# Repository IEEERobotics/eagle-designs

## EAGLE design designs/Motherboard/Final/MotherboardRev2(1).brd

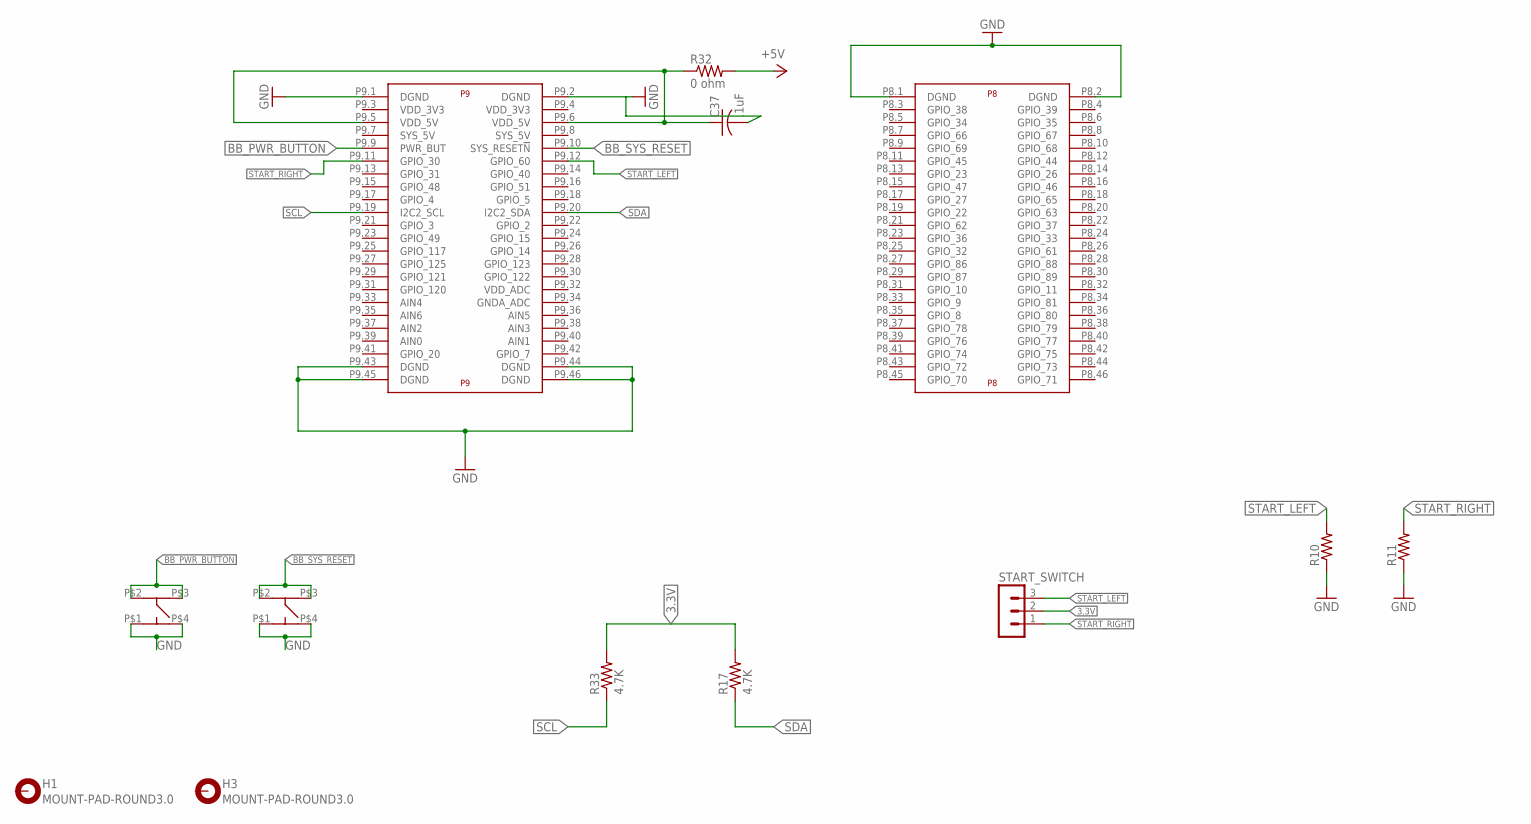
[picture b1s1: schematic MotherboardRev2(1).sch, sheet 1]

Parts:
C37: .1uF; C0402
H1, H3: MOUNT-PAD-ROUND3.0; 3,0-PAD
R10, R11: R-US_R0402; R0402
R17, R33: 4.7K; R0402
R32: 0 ohm; R0402
START_SWITCH: MA03-1
U$1: BEAGLE_BONE_BLACK_CAPE
U$13, U$14: Switch1; MC32882_FINAL

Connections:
3.3V: R17.2, R33.2, START_SWITCH.2; also elsewhere on the board
BB_PWR_BUTTON: U$1.P9.9 (PWR_BUT), U$13.P$2 (P2), U$13.P$3 (P3)
BB_SYS_RESET: U$1.P9.10 (SYS_RESET!N), U$14.P$2 (P2), U$14.P$3 (P3)
GND: C37.2, R10.1, R11.1, U$1.P8.1 (DGND), U$1.P8.2 (DGND), U$1.P9.1 (DGND), U$1.P9.2 (DGND), U$1.P9.43 (DGND), U$1.P9.44 (DGND), U$1.P9.45 (DGND), U$1.P9.46 (DGND), U$13.P$1 (P1), U$13.P$4 (P4), U$14.P$1 (P1), U$14.P$4 (P4); also elsewhere on the board
unnamed: C37.1, R32.1, U$1.P9.5 (VDD_5V), U$1.P9.6 (VDD_5V)
SCL: R33.1, U$1.P9.19 (I2C2_SCL); also elsewhere on the board
SDA: R17.1, U$1.P9.20 (I2C2_SDA); also elsewhere on the board
START_LEFT: R10.2, START_SWITCH.3, U$1.P9.12 (GPIO_60)
START_RIGHT: R11.2, START_SWITCH.1, U$1.P9.11 (GPIO_30)
VOUT1: R32.2; also elsewhere on the board

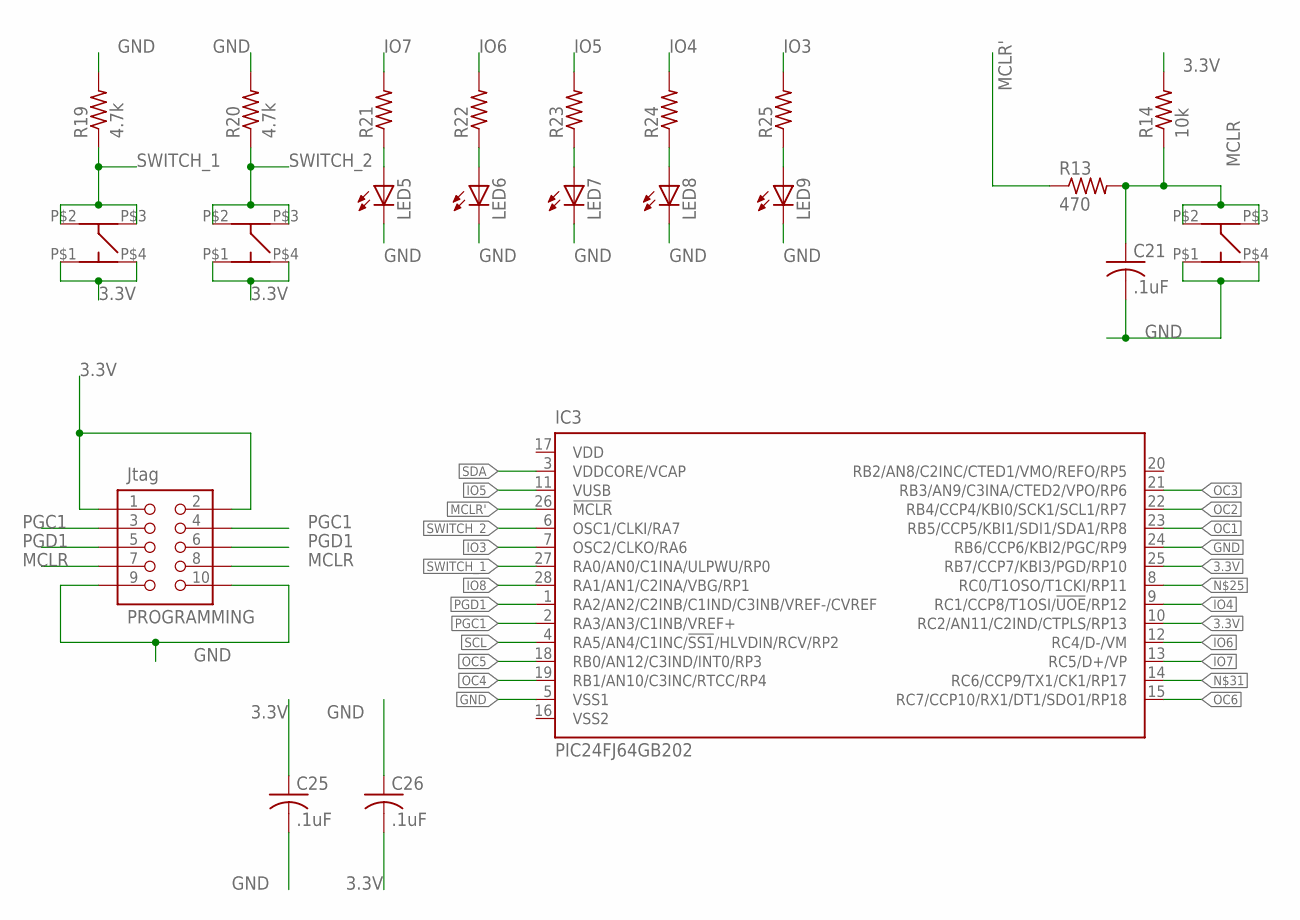
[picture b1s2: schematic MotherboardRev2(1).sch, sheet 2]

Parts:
C21, C25, C26: .1uF; C0402
IC3: PIC24FJ64GB202; QFN28-ML_6X6MM
LED5, LED6, LED7, LED8, LED9: LEDCHIPLED-0603-TTW; CHIPLED-0603-TTW
PROGRAMMING: Jtag; MOTHER-BOARD-REV5_10-PIN-SMD
R13: 470; R0402
R14: 10k; R0402
R19, R20: 4.7k; R0402
R21, R22, R23, R24, R25: R-US_R0402; R0402
U$5: Switch3; MC32882_FINAL
U$6: Switch1; MC32882_FINAL
U$7: Switch2; MC32882_FINAL

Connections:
3.3V: C25.1, C26.1, IC3.10 (RC2/AN11/C2IND/CTPLS/RP13), IC3.25 (RB7/CCP7/KBI3/PGD/RP10), PROGRAMMING.1, PROGRAMMING.2, R14.2, U$6.P$1 (P1), U$6.P$4 (P4), U$7.P$1 (P1), U$7.P$4 (P4); also elsewhere on the board
GND: C21.2, C25.2, C26.2, IC3.5 (VSS1), IC3.24 (RB6/CCP6/KBI2/PGC/RP9), LED5.C@1 (C), LED6.C@1 (C), LED7.C@1 (C), LED8.C@1 (C), LED9.C@1 (C), PROGRAMMING.9, PROGRAMMING.10, R19.2, R20.2, U$5.P$1 (P1), U$5.P$4 (P4); also elsewhere on the board
IO3: IC3.7 (OSC2/CLKO/RA6), R25.2
IO4: IC3.9 (RC1/CCP8/T1OSI/!UOE!/RP12), R24.2
IO5: IC3.11 (VUSB), R23.2
IO6: IC3.12 (RC4/D-/VM), R22.2
IO7: IC3.13 (RC5/D+/VP), R21.2
IO8: IC3.28 (RA1/AN1/C2INA/VBG/RP1)
MCLR: C21.1, PROGRAMMING.7, PROGRAMMING.8, R13.2, R14.1, U$5.P$2 (P2), U$5.P$3 (P3)
MCLR': IC3.26 (!MCLR), R13.1
unnamed: LED5.A@1 (A), R21.1
unnamed: LED6.A@1 (A), R22.1
unnamed: LED7.A@1 (A), R23.1
unnamed: LED8.A@1 (A), R24.1
unnamed: LED9.A@1 (A), R25.1
OC1: IC3.23 (RB5/CCP5/KBI1/SDI1/SDA1/RP8); also elsewhere on the board
OC2: IC3.22 (RB4/CCP4/KBI0/SCK1/SCL1/RP7); also elsewhere on the board
OC3: IC3.21 (RB3/AN9/C3INA/CTED2/VPO/RP6); also elsewhere on the board
OC4: IC3.19 (RB1/AN10/C3INC/RTCC/RP4); also elsewhere on the board
OC5: IC3.18 (RB0/AN12/C3IND/INT0/RP3); also elsewhere on the board
OC6: IC3.15 (RC7/CCP10/RX1/DT1/SDO1/RP18); also elsewhere on the board
PGC1: IC3.2 (RA3/AN3/C1INB/VREF+), PROGRAMMING.3, PROGRAMMING.4
PGD1: IC3.1 (RA2/AN2/C2INB/C1IND/C3INB/VREF-/CVREF), PROGRAMMING.5, PROGRAMMING.6
SCL: IC3.4 (RA5/AN4/C1INC/!SS1!/HLVDIN/RCV/RP2); also elsewhere on the board
SDA: IC3.3 (VDDCORE/VCAP); also elsewhere on the board
SWITCH_1: IC3.27 (RA0/AN0/C1INA/ULPWU/RP0), R19.1, U$6.P$2 (P2), U$6.P$3 (P3)
SWITCH_2: IC3.6 (OSC1/CLKI/RA7), R20.1, U$7.P$2 (P2), U$7.P$3 (P3)

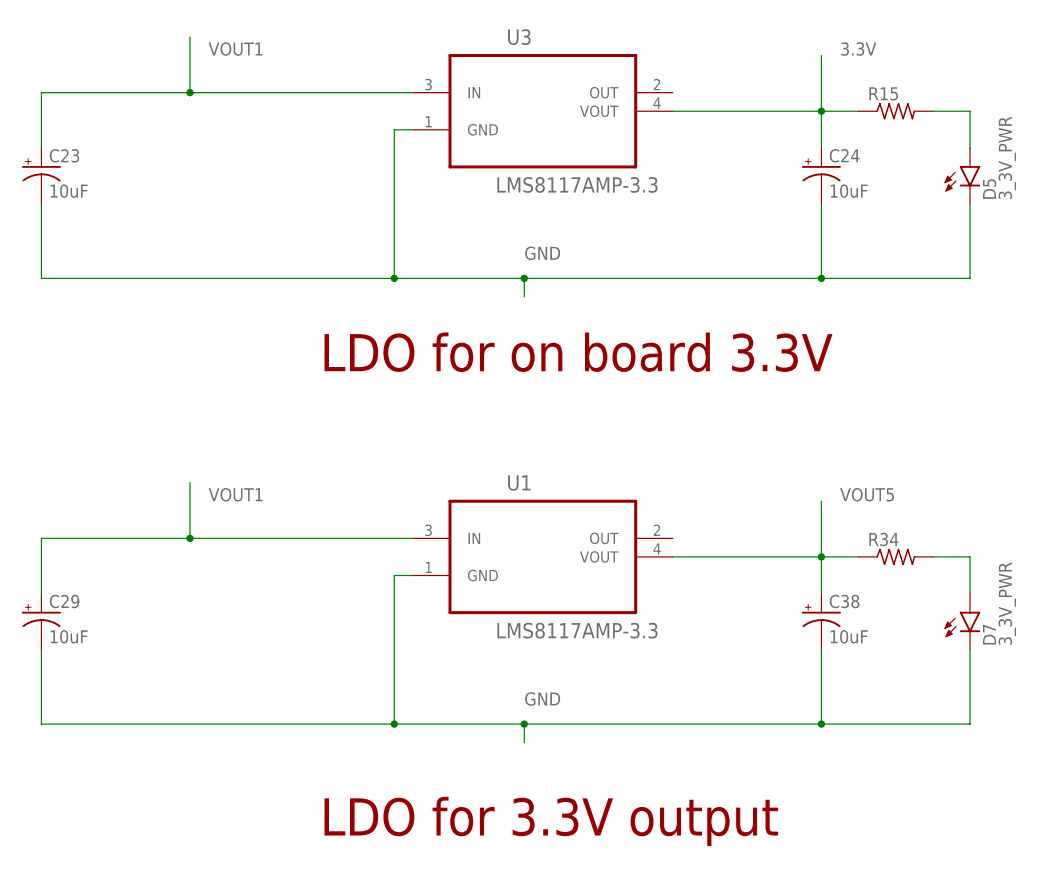
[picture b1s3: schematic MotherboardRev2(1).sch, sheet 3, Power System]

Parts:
C23, C24, C29, C38: 10uF; EIA3216
D5, D7: 3_3V_PWR; FKIT-LED-1206
R15, R34: R-US_R0805W; R0805W
U1, U3: LMS8117AMP-3.3; SOT230P696X180-4N

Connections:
3.3V: C24.A (+), R15.1, U3.4 (VOUT); also elsewhere on the board
GND: C23.C (-), C24.C (-), C29.C (-), C38.C (-), D5.C, D7.C, U1.1 (GND), U3.1 (GND); also elsewhere on the board
unnamed: D5.A, R15.2
unnamed: D7.A, R34.2
VOUT1: C23.A (+), C29.A (+), U1.3 (IN), U3.3 (IN); also elsewhere on the board
VOUT5: C38.A (+), R34.1, U1.4 (VOUT); also elsewhere on the board

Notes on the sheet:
LDO for on board 3.3V
LDO for 3.3V output

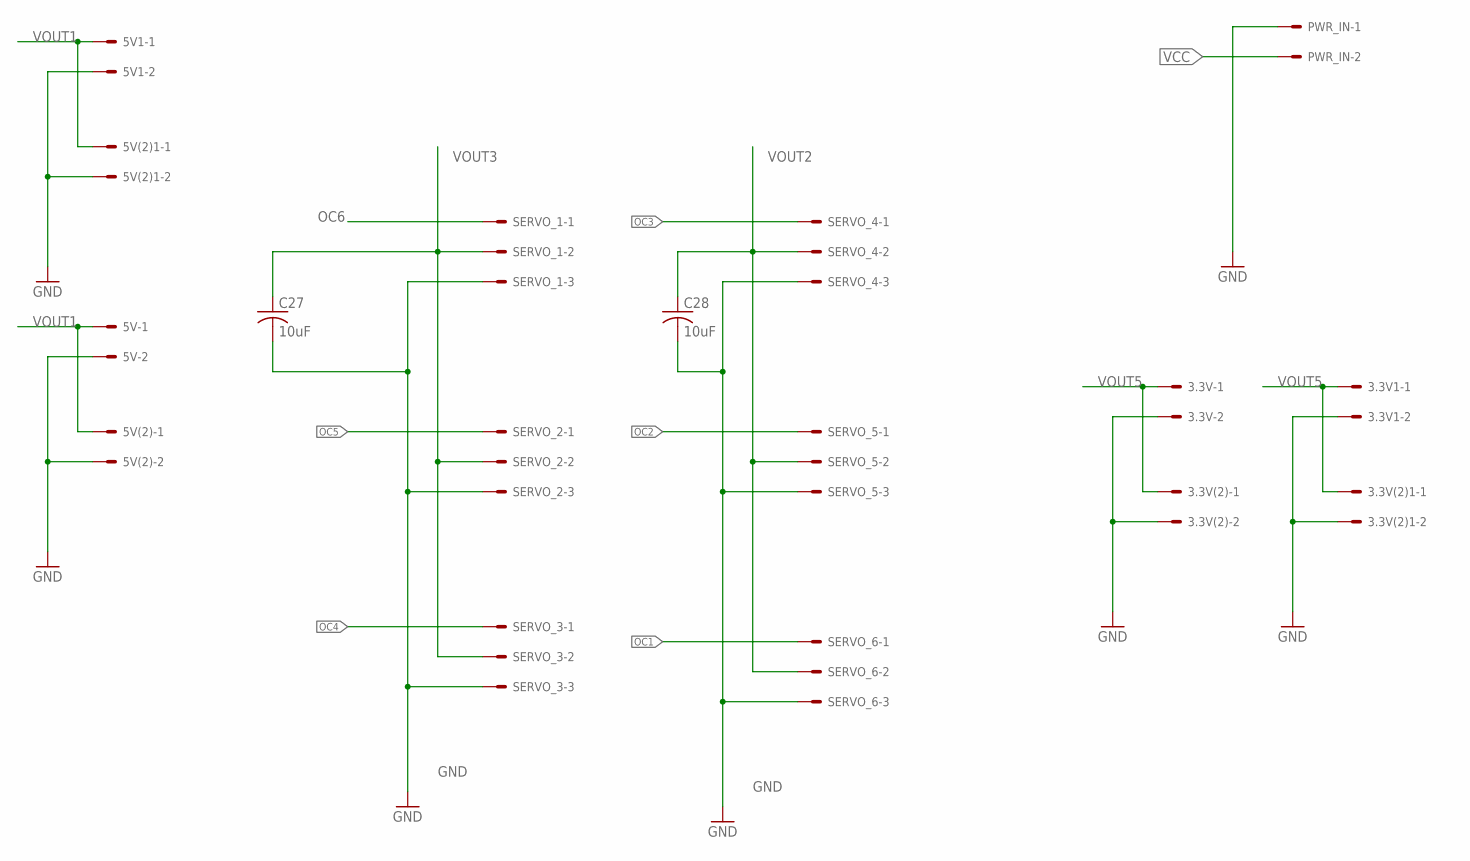
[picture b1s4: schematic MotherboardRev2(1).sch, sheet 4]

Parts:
3.3V, 3.3V1, 3.3V(2), 3.3V(2)1, 5V, 5V1, 5V(2), 5V(2)1: 22-05-7028-02; 7395-02
C27, C28: 10uF; C0805
PWR_IN: 555X-2H; 5569-2
SERVO_1, SERVO_2, SERVO_3, SERVO_4, SERVO_5, SERVO_6: 22-05-7038-03; 7395-03

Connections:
GND: 3.3V.2, 3.3V1.2, 3.3V(2).2, 3.3V(2)1.2, 5V.2, 5V1.2, 5V(2).2, 5V(2)1.2, C27.2, C28.2, PWR_IN.1, SERVO_1.3, SERVO_2.3, SERVO_3.3, SERVO_4.3, SERVO_5.3, SERVO_6.3; also elsewhere on the board
OC1: SERVO_6.1; also elsewhere on the board
OC2: SERVO_5.1; also elsewhere on the board
OC3: SERVO_4.1; also elsewhere on the board
OC4: SERVO_3.1; also elsewhere on the board
OC5: SERVO_2.1; also elsewhere on the board
OC6: SERVO_1.1; also elsewhere on the board
VCC: PWR_IN.2; also elsewhere on the board
VOUT1: 5V.1, 5V1.1, 5V(2).1, 5V(2)1.1; also elsewhere on the board
VOUT2: C28.1, SERVO_4.2, SERVO_5.2, SERVO_6.2; also elsewhere on the board
VOUT3: C27.1, SERVO_1.2, SERVO_2.2, SERVO_3.2; also elsewhere on the board
VOUT5: 3.3V.1, 3.3V1.1, 3.3V(2).1, 3.3V(2)1.1; also elsewhere on the board

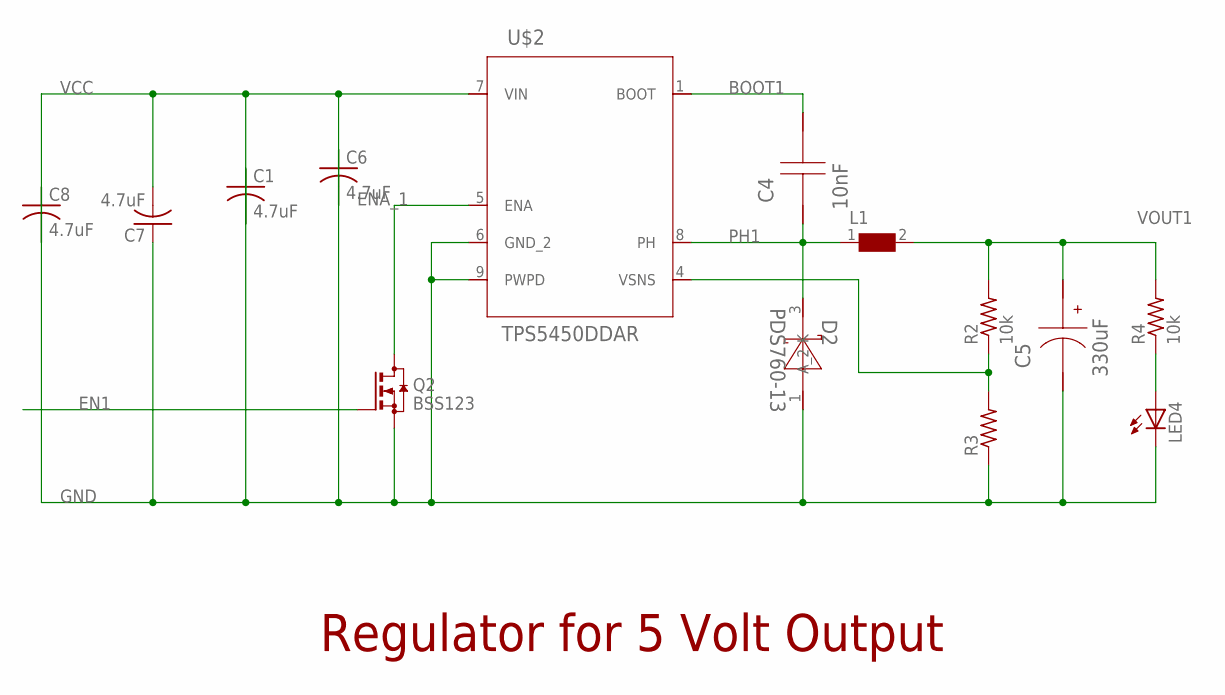
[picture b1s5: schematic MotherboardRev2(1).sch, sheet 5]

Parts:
C1, C6, C7, C8: 4.7uF; C0805
C4: 10nF; 0805
C5: 330uF; SM_RADIAL_10AMM
D2: PDS760-13; POWERDI5
L1: WE-HCC-7443331000_1090; WE-HCC_1090
LED4: LEDSML1206; SML1206
Q2: BSS123; SOT23
R2, R4: 10k; R1206
R3: R-US_R1206; R1206
U$2: TPS5450DDAR; R-PDSO-G8

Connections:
BOOT1: C4.1, U$2.1 (BOOT)
EN1: Q2.1 (G)
ENA_1: Q2.3 (D), U$2.5 (ENA)
GND: C1.1, C5.2 (-), C6.1, C7.1, C8.1, D2.1 (A_2), LED4.C, Q2.2 (S), R3.1, U$2.6 (GND_2), U$2.9 (PWPD); also elsewhere on the board
unnamed: LED4.A, R4.1
PH1: C4.2, D2.3 (K), L1.1, U$2.8 (PH)
VCC: C1.2, C6.2, C7.2, C8.2, U$2.7 (VIN); also elsewhere on the board
VOUT1: C5.1 (+), L1.2, R2.2, R4.2; also elsewhere on the board
VSNS1: R2.1, R3.2, U$2.4 (VSNS)

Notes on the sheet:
Regulator for 5 Volt Output

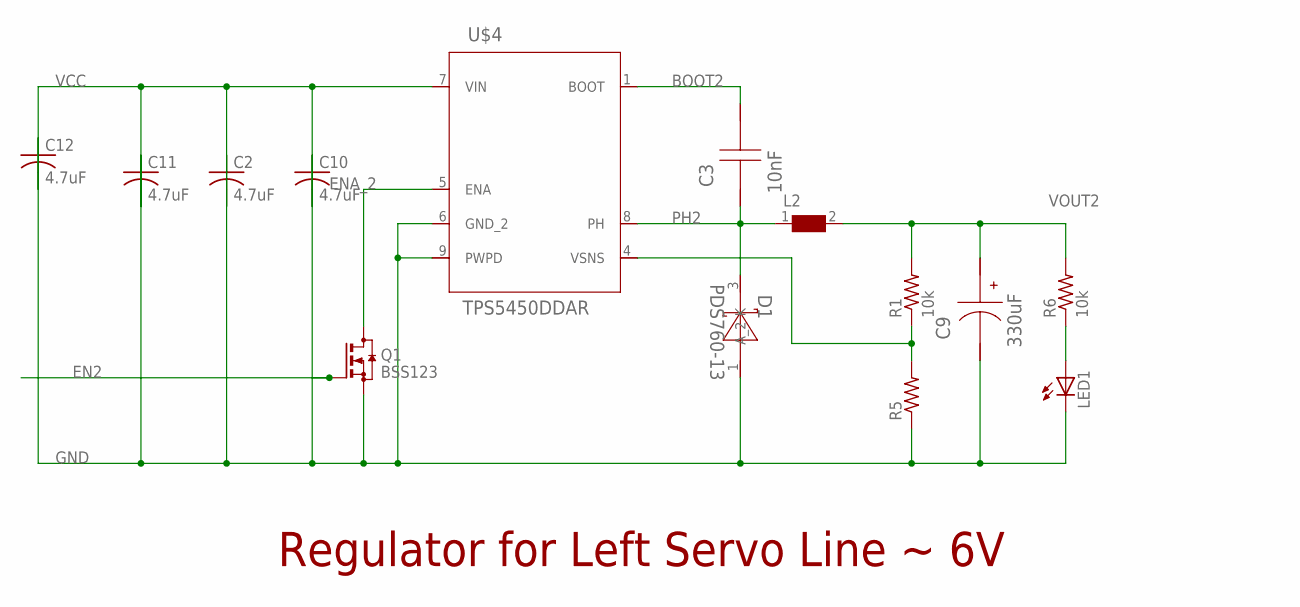
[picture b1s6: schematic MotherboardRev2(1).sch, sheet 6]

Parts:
C2, C10, C11, C12: 4.7uF; C0805
C3: 10nF; 0805
C9: 330uF; SM_RADIAL_10AMM
D1: PDS760-13; POWERDI5
L2: WE-HCC-7443331000_1090; WE-HCC_1090
LED1: LEDSML1206; SML1206
Q1: BSS123; SOT23
R1, R6: 10k; R1206
R5: R-US_R1206; R1206
U$4: TPS5450DDAR; R-PDSO-G8

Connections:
BOOT2: C3.1, U$4.1 (BOOT)
EN2: Q1.1 (G)
ENA_2: Q1.3 (D), U$4.5 (ENA)
GND: C2.1, C9.2 (-), C10.1, C11.1, C12.1, D1.1 (A_2), LED1.C, Q1.2 (S), R5.1, U$4.6 (GND_2), U$4.9 (PWPD); also elsewhere on the board
unnamed: LED1.A, R6.1
PH2: C3.2, D1.3 (K), L2.1, U$4.8 (PH)
VCC: C2.2, C10.2, C11.2, C12.2, U$4.7 (VIN); also elsewhere on the board
VOUT2: C9.1 (+), L2.2, R1.2, R6.2; also elsewhere on the board
VSNS2: R1.1, R5.2, U$4.4 (VSNS)

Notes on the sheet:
Regulator for Left Servo Line ~ 6V

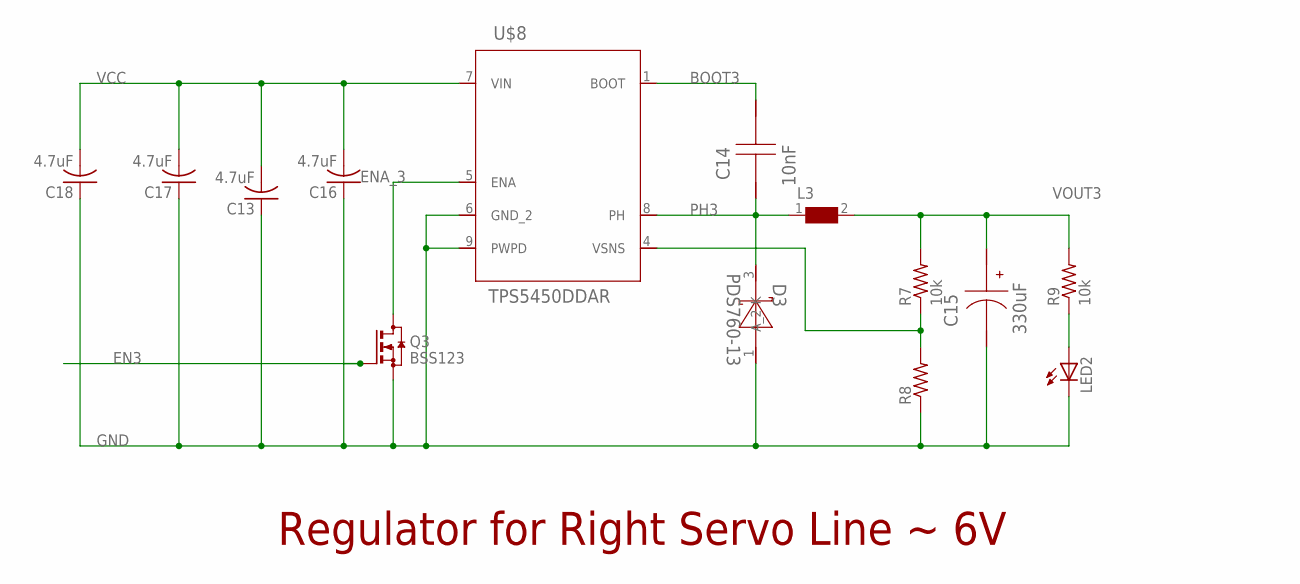
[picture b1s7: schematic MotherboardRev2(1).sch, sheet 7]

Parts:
C13, C16, C17, C18: 4.7uF; C0805
C14: 10nF; 0805
C15: 330uF; SM_RADIAL_10AMM
D3: PDS760-13; POWERDI5
L3: WE-HCC-7443331000_1090; WE-HCC_1090
LED2: LEDSML1206; SML1206
Q3: BSS123; SOT23
R7, R9: 10k; R1206
R8: R-US_R1206; R1206
U$8: TPS5450DDAR; R-PDSO-G8

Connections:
BOOT3: C14.1, U$8.1 (BOOT)
EN3: Q3.1 (G)
ENA_3: Q3.3 (D), U$8.5 (ENA)
GND: C13.1, C15.2 (-), C16.1, C17.1, C18.1, D3.1 (A_2), LED2.C, Q3.2 (S), R8.1, U$8.6 (GND_2), U$8.9 (PWPD); also elsewhere on the board
unnamed: LED2.A, R9.1
PH3: C14.2, D3.3 (K), L3.1, U$8.8 (PH)
VCC: C13.2, C16.2, C17.2, C18.2, U$8.7 (VIN); also elsewhere on the board
VOUT3: C15.1 (+), L3.2, R7.2, R9.2; also elsewhere on the board
VSNS3: R7.1, R8.2, U$8.4 (VSNS)

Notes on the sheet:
Regulator for Right Servo Line ~ 6V

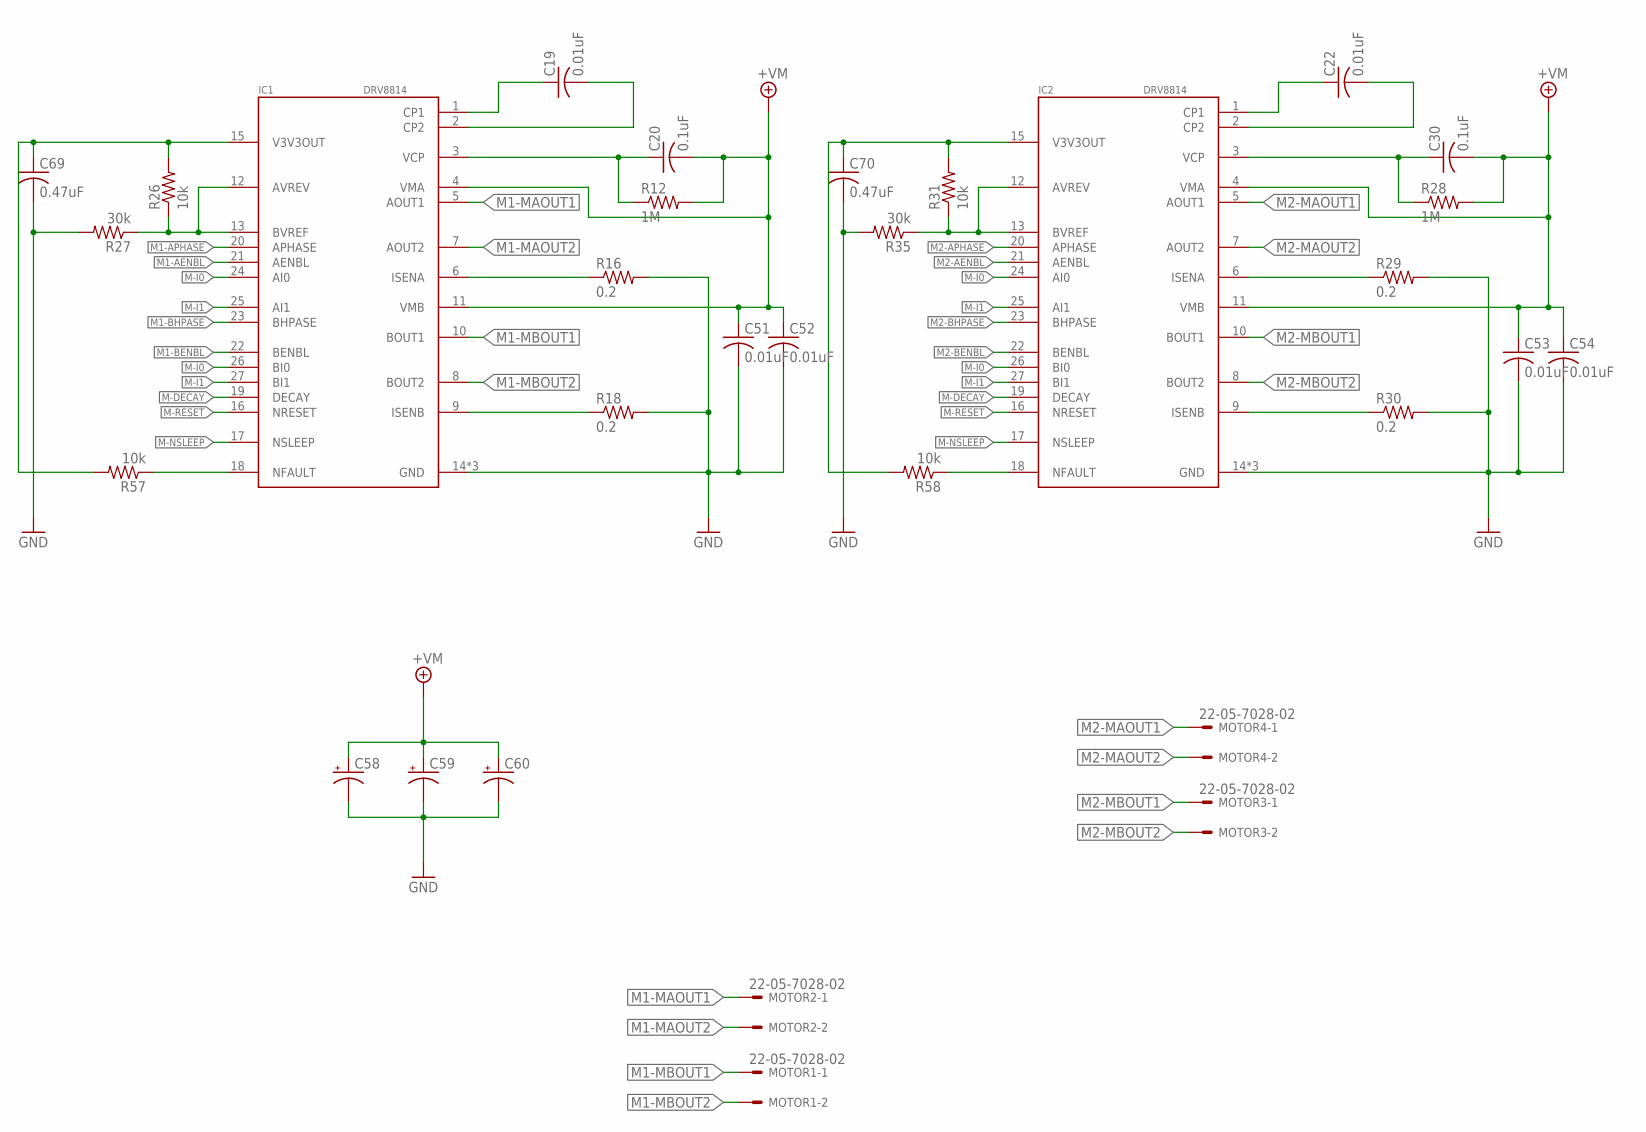
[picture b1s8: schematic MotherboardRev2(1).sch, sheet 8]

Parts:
C19, C22, C51, C52, C53, C54: 0.01uF; C0402
C20, C30: 0.1uF; C0402
C58, C59, C60: CPOL-US153CLV-0605; 153CLV-0605
C69, C70: 0.47uF; C0402
IC1, IC2: DRV8814; TSSOP-28
MOTOR1, MOTOR2, MOTOR3, MOTOR4: 22-05-7028-02; 7395-02
R12, R28: 1M; R0402
R16, R18, R29, R30: 0.2; R0402
R26, R31, R57, R58: 10k; R0402
R27, R35: 30k; R0402

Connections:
+7V: C20.2, C30.2, C51.1, C52.1, C53.1, C54.1, C58.+, C59.+, C60.+, IC1.4 (VMA), IC1.11 (VMB), IC2.4 (VMA), IC2.11 (VMB), R12.2, R28.2; also elsewhere on the board
GND: C51.2, C52.2, C53.2, C54.2, C58.-, C59.-, C60.-, C69.2, C70.2, IC1.14 (GND), IC1.28 (GND), IC1.EXP (GND), IC2.14 (GND), IC2.28 (GND), IC2.EXP (GND), R16.2, R18.2, R27.2, R29.2, R30.2, R35.2; also elsewhere on the board
M1-AENBL: IC1.21 (AENBL); also elsewhere on the board
M1-APHASE: IC1.20 (APHASE); also elsewhere on the board
M1-BENBL: IC1.22 (BENBL); also elsewhere on the board
M1-BHPASE: IC1.23 (BHPASE); also elsewhere on the board
M1-MAOUT1: IC1.5 (AOUT1), MOTOR2.1
M1-MAOUT2: IC1.7 (AOUT2), MOTOR2.2
M1-MBOUT1: IC1.10 (BOUT1), MOTOR1.1
M1-MBOUT2: IC1.8 (BOUT2), MOTOR1.2
M2-AENBL: IC2.21 (AENBL); also elsewhere on the board
M2-APHASE: IC2.20 (APHASE); also elsewhere on the board
M2-BENBL: IC2.22 (BENBL); also elsewhere on the board
M2-BHPASE: IC2.23 (BHPASE); also elsewhere on the board
M2-MAOUT1: IC2.5 (AOUT1), MOTOR4.1
M2-MAOUT2: IC2.7 (AOUT2), MOTOR4.2
M2-MBOUT1: IC2.10 (BOUT1), MOTOR3.1
M2-MBOUT2: IC2.8 (BOUT2), MOTOR3.2
M-DECAY: IC1.19 (DECAY), IC2.19 (DECAY); also elsewhere on the board
M-I0: IC1.24 (AI0), IC1.26 (BI0), IC2.24 (AI0), IC2.26 (BI0); also elsewhere on the board
M-I1: IC1.25 (AI1), IC1.27 (BI1), IC2.25 (AI1), IC2.27 (BI1); also elsewhere on the board
M-NSLEEP: IC1.17 (NSLEEP), IC2.17 (NSLEEP); also elsewhere on the board
M-RESET: IC1.16 (NRESET), IC2.16 (NRESET); also elsewhere on the board
unnamed: C19.2, IC1.2 (CP2)
unnamed: C19.1, IC1.1 (CP1)
unnamed: C20.1, IC1.3 (VCP), R12.1
unnamed: IC1.6 (ISENA), R16.1
unnamed: IC1.9 (ISENB), R18.1
unnamed: IC1.12 (AVREV), IC1.13 (BVREF), R26.1, R27.1
unnamed: C22.2, IC2.2 (CP2)
unnamed: C22.1, IC2.1 (CP1)
unnamed: C30.1, IC2.3 (VCP), R28.1
unnamed: IC2.6 (ISENA), R29.1
unnamed: IC2.9 (ISENB), R30.1
unnamed: IC2.12 (AVREV), IC2.13 (BVREF), R31.1, R35.1
unnamed: IC1.18 (NFAULT), R57.1
unnamed: C69.1, IC1.15 (V3V3OUT), R26.2, R57.2
unnamed: IC2.18 (NFAULT), R58.1
unnamed: C70.1, IC2.15 (V3V3OUT), R31.2, R58.2

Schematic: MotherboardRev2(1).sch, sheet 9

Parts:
C31, C32, C39, C40: 1nF; C0402
C33, C45, C46, C47, C48, C49, C50: 0.1uF; C0402
C34, C35, C36, C42, C43, C44: 0.22uF; C0402
C41: .1uF; C0402
R36, R37, R44, R45: 0.1; R0402
R38, R39, R46, R47: 47k; R0402
R40, R41, R42, R43, R48, R49, R50, R51: 10k; R0402
STEP1, STEP2: 22-05-7048-04; 7395-04
U2, U4: DRV8811PWP; SOP65P640X120-29N

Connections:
3.3V: C49.1, C50.1, R40.1, R43.1, R48.1, R51.1, U2.10 (VCC), U4.10 (VCC); also elsewhere on the board
+7V: C36.1, C44.1, C45.1, C46.1, C47.1, C48.1, U2.15 (VMB), U2.28 (VMA), U4.15 (VMB), U4.28 (VMA); also elsewhere on the board
GND: C31.2, C32.2, C33.2, C35.2, C39.2, C40.2, C41.2, C43.2, C45.2, C46.2, C47.2, C48.2, C49.2, C50.2, R36.2, R37.2, R38.2, R39.2, R41.2, R42.2, R44.2, R45.2, R46.2, R47.2, R49.2, R50.2, U2.7 (GND_2), U2.21 (GND), U2.29 (EP), U4.7 (GND_2), U4.21 (GND), U4.29 (EP); also elsewhere on the board
M-NSLEEP: U2.27 (SLEEPN), U4.27 (SLEEPN); also elsewhere on the board
M-RESET: U2.17 (RESETN), U4.17 (RESETN); also elsewhere on the board
unnamed: R37.1, U2.14 (ISENB)
unnamed: R36.1, U2.1 (ISENA)
unnamed: C31.1, R38.1, U2.6 (RCA)
unnamed: C32.1, R39.1, U2.9 (RCB)
unnamed: C33.1, R40.2, R41.1, U2.5 (DECAY)
unnamed: R42.1, R43.2, U2.8 (VREF)
unnamed: C34.1, U2.23 (CP1)
unnamed: C34.2, U2.24 (CP2)
unnamed: C35.1, U2.20 (VGD)
unnamed: C36.2, U2.22 (VCP)
unnamed: R45.1, U4.14 (ISENB)
unnamed: R44.1, U4.1 (ISENA)
unnamed: C39.1, R46.1, U4.6 (RCA)
unnamed: C40.1, R47.1, U4.9 (RCB)
unnamed: C41.1, R48.2, R49.1, U4.5 (DECAY)
unnamed: R50.1, R51.2, U4.8 (VREF)
unnamed: C42.1, U4.23 (CP1)
unnamed: C42.2, U4.24 (CP2)
unnamed: C43.1, U4.20 (VGD)
unnamed: C44.2, U4.22 (VCP)
S1-AOUT1: STEP1.4, U2.4 (AOUT1)
S1-AOUT2: STEP1.1, U2.25 (AOUT2)
S1-BOUT1: STEP1.3, U2.11 (BOUT1)
S1-BOUT2: STEP1.2, U2.18 (BOUT2)
S1-DIR: U2.3 (DIR); also elsewhere on the board
S1-ENABLEN: U2.26 (ENABLEN); also elsewhere on the board
S1-HOME: U2.2 (HOME); also elsewhere on the board
S1-STEP: U2.19 (STEP); also elsewhere on the board
S2-AOUT1: STEP2.4, U4.4 (AOUT1)
S2-AOUT2: STEP2.1, U4.25 (AOUT2)
S2-BOUT1: STEP2.3, U4.11 (BOUT1)
S2-BOUT2: STEP2.2, U4.18 (BOUT2)
S2-DIR: U4.3 (DIR); also elsewhere on the board
S2-ENABLEN: U4.26 (ENABLEN); also elsewhere on the board
S2-HOME: U4.2 (HOME); also elsewhere on the board
S2-STEP: U4.19 (STEP); also elsewhere on the board
S-SRN: U2.16 (SRN), U4.16 (SRN); also elsewhere on the board
USM0: U2.13 (USM0), U4.13 (USM0); also elsewhere on the board
USM1: U2.12 (USM1), U4.12 (USM1); also elsewhere on the board

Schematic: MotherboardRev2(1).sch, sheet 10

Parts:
C55: 1uF; C0402
C56, C57: 0.1uF; C0402
C61: 10uF; C0805
C68: .1uF; C0402
H2, H4: MOUNT-PAD-ROUND3.0; 3,0-PAD
IC4: PIC24FJ256GB106; TQFP64-10X10
MOTIN1, MOTIN2, MOTIN3, MOTIN4: 22-05-7048-04; 7395-04
PROGRAMMING1: Jtag; MOTHER-BOARD-REV5_10-PIN-SMD
PWR_IN(2): 555X-2H; 5569-2
R55: 100; R0402
R56: 10k; R0402
SERVO_7, SERVO_8, SERVO_9: 22-05-7038-03; 7395-03
TP1, TP2: PTR1B1,27; B1,27
U$9: Switch3; MC32882_FINAL

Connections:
3.3V: C55.1, C56.1, C57.1, IC4.10 (VDD), IC4.26 (VDD), IC4.38 (VDD), PROGRAMMING1.1, PROGRAMMING1.2, R56.2; also elsewhere on the board
+7V: C61.1, H4.B3,0, MOTIN1.2, MOTIN2.2, MOTIN3.2, MOTIN4.2, SERVO_7.2, SERVO_8.2, SERVO_9.2; also elsewhere on the board
AVDD: IC4.19 (AVDD)
AVSS: IC4.20 (AVSS)
CHANNEL_A_1: IC4.4 (RG6), MOTIN1.4
CHANNEL_A_2: IC4.22 (RB9), MOTIN2.3
CHANNEL_A_3: IC4.18 (RB7), MOTIN3.3
CHANNEL_A_4: IC4.8 (RG9), MOTIN4.3
CHANNEL_B_1: IC4.5 (RG7), MOTIN1.3
CHANNEL_B_2: IC4.21 (RB8), MOTIN2.4
CHANNEL_B_3: IC4.17 (RB6), MOTIN3.4
CHANNEL_B_4: IC4.6 (RG8), MOTIN4.4
GND: C55.2, C56.2, C57.2, C61.2, C68.2, IC4.9 (VSS), IC4.25 (VSS), IC4.41 (VSS), MOTIN1.1, MOTIN2.1, MOTIN3.1, MOTIN4.1, PROGRAMMING1.9, PROGRAMMING1.10, PWR_IN(2).1, SERVO_7.3, SERVO_8.3, SERVO_9.3, U$9.P$1 (P1), U$9.P$4 (P4); also elsewhere on the board
M1-AENBL: IC4.47 (RC13); also elsewhere on the board
M1-APHASE: IC4.48 (RC14); also elsewhere on the board
M1-BENBL: IC4.46 (RD0); also elsewhere on the board
M1-BHPASE: IC4.45 (RD11); also elsewhere on the board
M2-AENBL: IC4.39 (RC12); also elsewhere on the board
M2-APHASE: IC4.43 (RD9); also elsewhere on the board
M2-BENBL: IC4.37 (RG2); also elsewhere on the board
M2-BHPASE: IC4.42 (RD8); also elsewhere on the board
M-DECAY: IC4.49 (RD1); also elsewhere on the board
M-I0: IC4.44 (RD10); also elsewhere on the board
M-I1: IC4.40 (RC15); also elsewhere on the board
M-NSLEEP: IC4.58 (RF0); also elsewhere on the board
M-RESET: IC4.60 (RE0); also elsewhere on the board
M_MCLR: C68.1, PROGRAMMING1.7, PROGRAMMING1.8, R55.2, R56.1, U$9.P$2 (P2), U$9.P$3 (P3)
M_MCLR': IC4.7 (!MCLR), R55.1
M_PGC1: IC4.15 (RB1), PROGRAMMING1.3, PROGRAMMING1.4
M_PGD1: IC4.16 (RB0), PROGRAMMING1.5, PROGRAMMING1.6
OC1': IC4.33 (RF3), SERVO_7.1
OC2': IC4.32 (RF5), SERVO_8.1
OC3': IC4.31 (RF4), SERVO_9.1
S1-DIR: IC4.64 (RE4); also elsewhere on the board
S1-ENABLEN: IC4.55 (RD7); also elsewhere on the board
S1-HOME: IC4.63 (RE3); also elsewhere on the board
S1-STEP: IC4.53 (RD5); also elsewhere on the board
S2-DIR: IC4.54 (RD6); also elsewhere on the board
S2-ENABLEN: IC4.51 (RD3); also elsewhere on the board
S2-HOME: IC4.52 (RD4); also elsewhere on the board
S2-STEP: IC4.50 (RD2); also elsewhere on the board
S-SRN: IC4.59 (RF1); also elsewhere on the board
SCL: IC4.2 (RE6), TP1.TP; also elsewhere on the board
SDA: IC4.3 (RE7), TP2.TP; also elsewhere on the board
USM0: IC4.62 (RE2); also elsewhere on the board
USM1: IC4.61 (RE1); also elsewhere on the board
VCC: PWR_IN(2).2; also elsewhere on the board
VDDCORE: IC4.56 (VDDCORE)

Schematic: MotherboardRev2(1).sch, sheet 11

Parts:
C62, C65, C66, C67: 4.7uF; 1206
C63: 10nF; 0805
C64: 330uF; SM_RADIAL_10AMM
D4: PDS760-13; POWERDI5
L4: WE-HCC-7443331000_1090; WE-HCC_1090
LED3: LEDCHIP-LED0603; CHIP-LED0603
POWER_ON: LEDCHIP-LED0603; CHIP-LED0603
R52, R54, R59: 10k; R0402
R53: R-US_R0402; R0402
U$3: TPS5450DDAR; R-PDSO-G8
U$10: LOGO

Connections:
+7V: C64.1 (+), L4.2, R52.2, R54.2; also elsewhere on the board
BOOT_VM: C63.1, U$3.1 (BOOT)
GND: C62.1, C64.2 (-), C65.1, C66.1, C67.1, D4.1 (A_2), LED3.C, POWER_ON.C, R53.1, U$3.6 (GND_2), U$3.9 (PWPD); also elsewhere on the board
unnamed: LED3.A, R54.1
unnamed: POWER_ON.A, R59.1
PH_VM: C63.2, D4.3 (K), L4.1, U$3.8 (PH)
VCC: C62.2, C65.2, C66.2, C67.2, R59.2, U$3.7 (VIN); also elsewhere on the board
VSNS_VM: R52.1, R53.2, U$3.4 (VSNS)

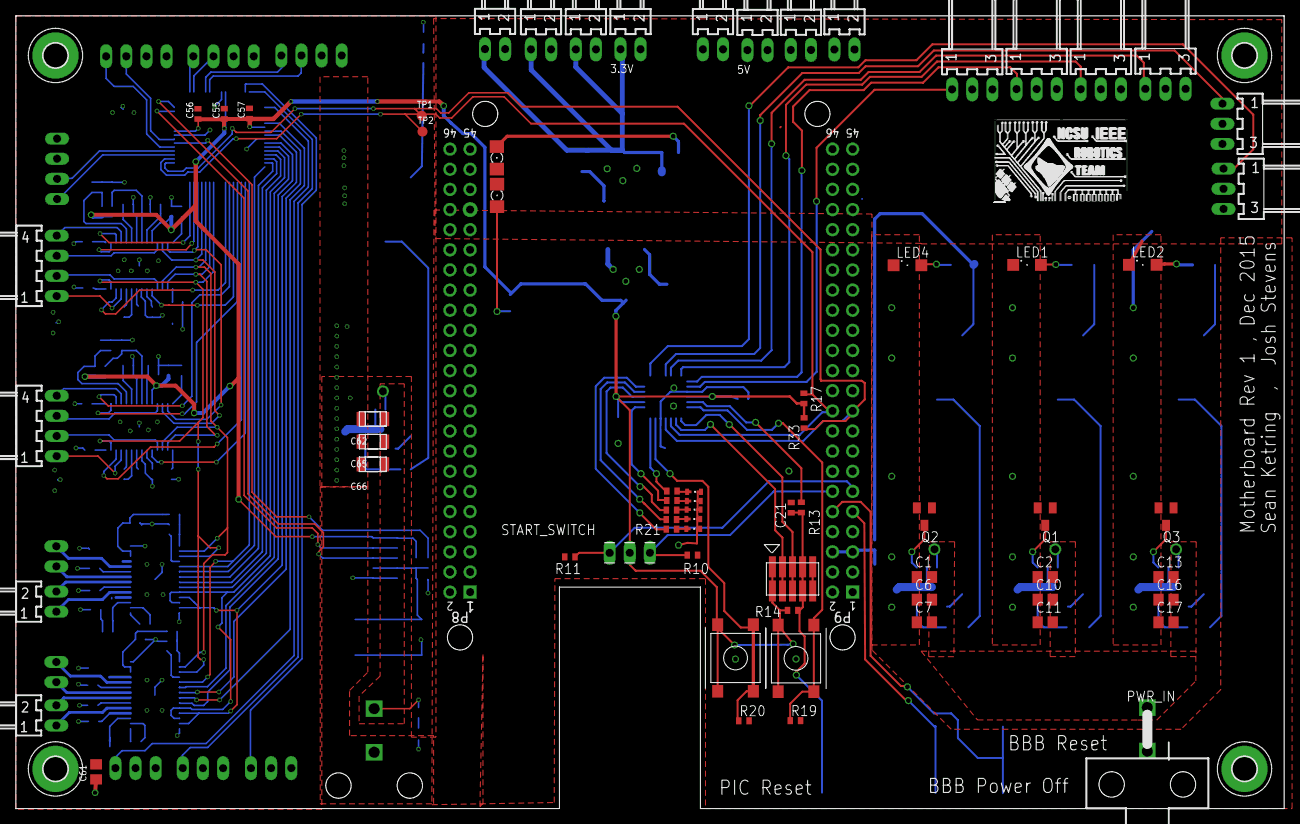
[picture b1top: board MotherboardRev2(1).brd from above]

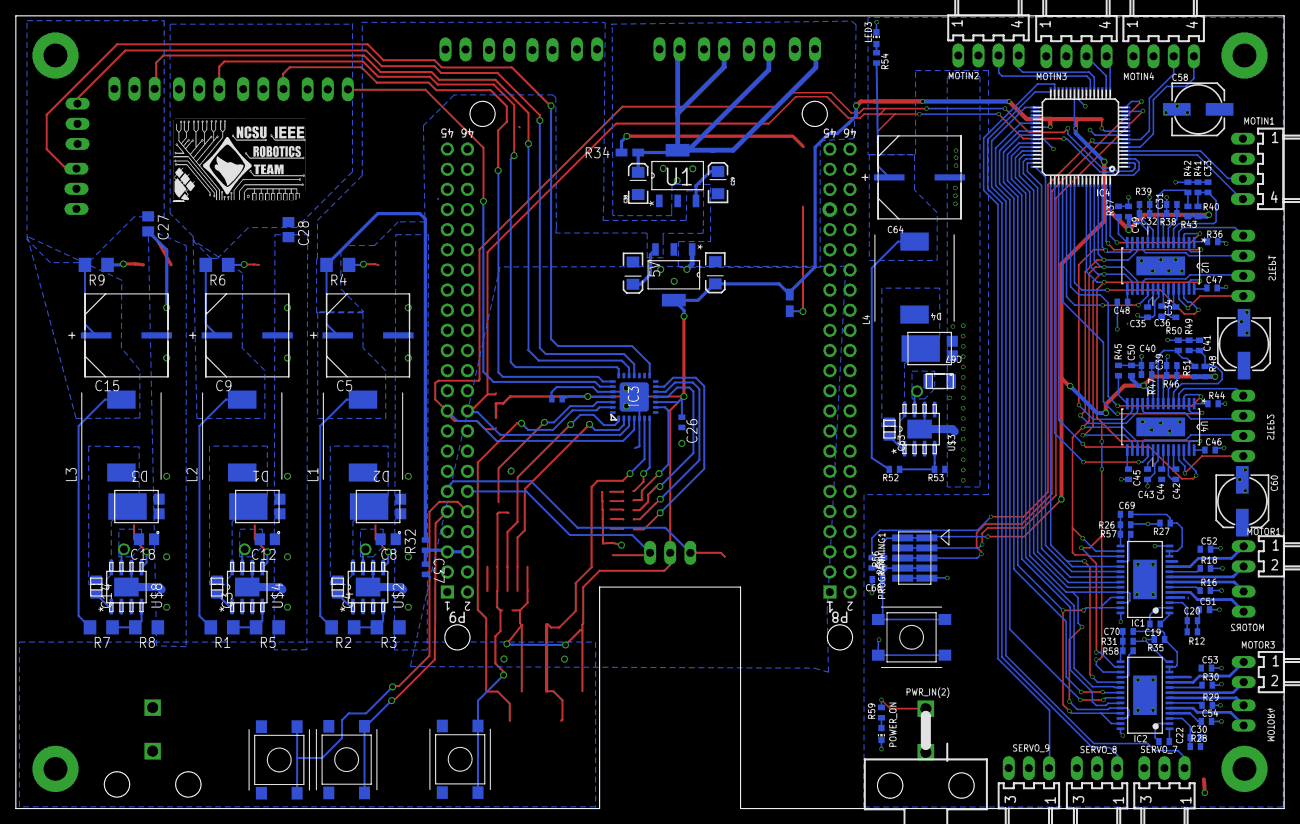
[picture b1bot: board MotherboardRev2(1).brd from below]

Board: 2 copper layers, 160.0 x 100.0 mm, 212 parts (137 on the bottom side), 150 nets.

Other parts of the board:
U$11, U$12: LOGO

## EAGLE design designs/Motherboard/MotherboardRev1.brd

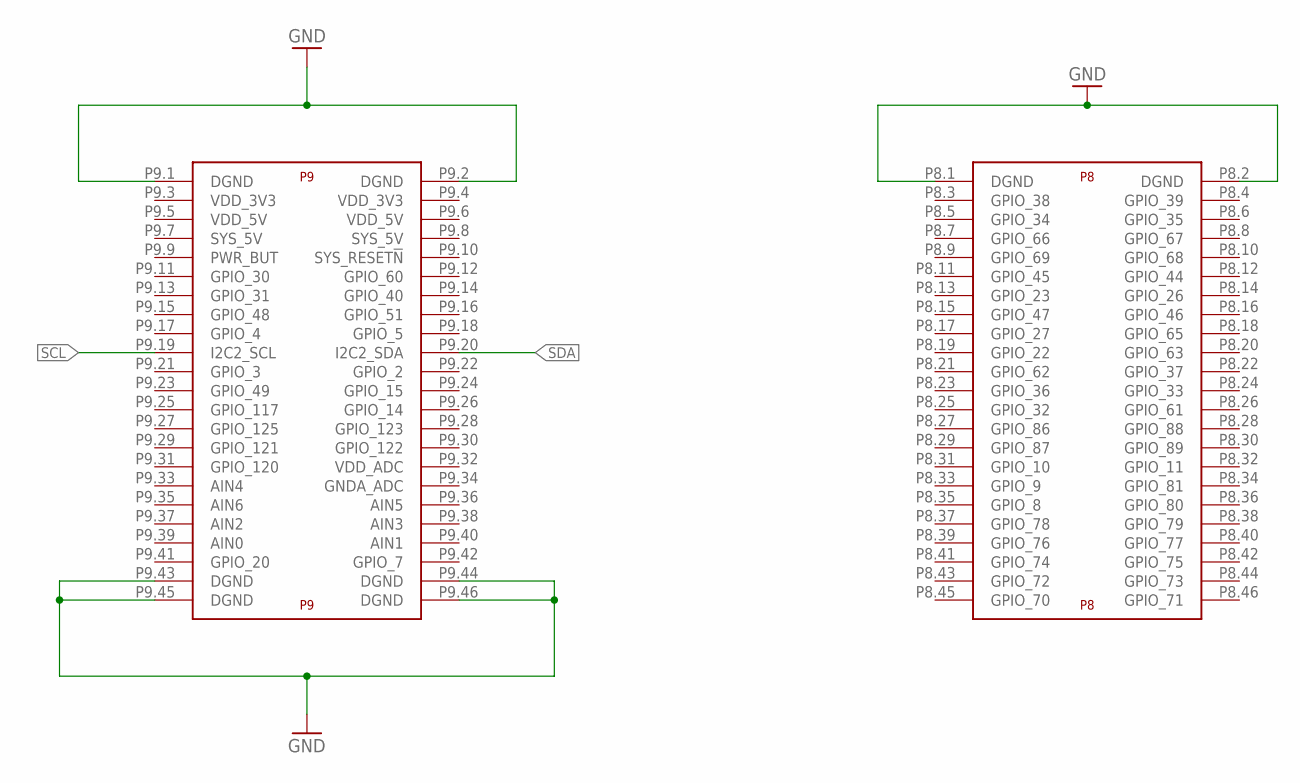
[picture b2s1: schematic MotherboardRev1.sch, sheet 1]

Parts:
U$1: BEAGLE_BONE_BLACK_CAPE

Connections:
GND: U$1.P8.1 (DGND), U$1.P8.2 (DGND), U$1.P9.1 (DGND), U$1.P9.2 (DGND), U$1.P9.43 (DGND), U$1.P9.44 (DGND), U$1.P9.45 (DGND), U$1.P9.46 (DGND); also elsewhere on the board
SCL: U$1.P9.19 (I2C2_SCL); also elsewhere on the board
SDA: U$1.P9.20 (I2C2_SDA); also elsewhere on the board

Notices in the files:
parts and their libraries:
SparkFun-Capacitors: Licensing: Creative Commons ShareAlike 4.0 International - https://creativecommons.org/licenses/by-sa/4.0
